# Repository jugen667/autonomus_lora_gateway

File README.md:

# autonomus_lora_gateway
Creation of an autonomous LoRa gateway

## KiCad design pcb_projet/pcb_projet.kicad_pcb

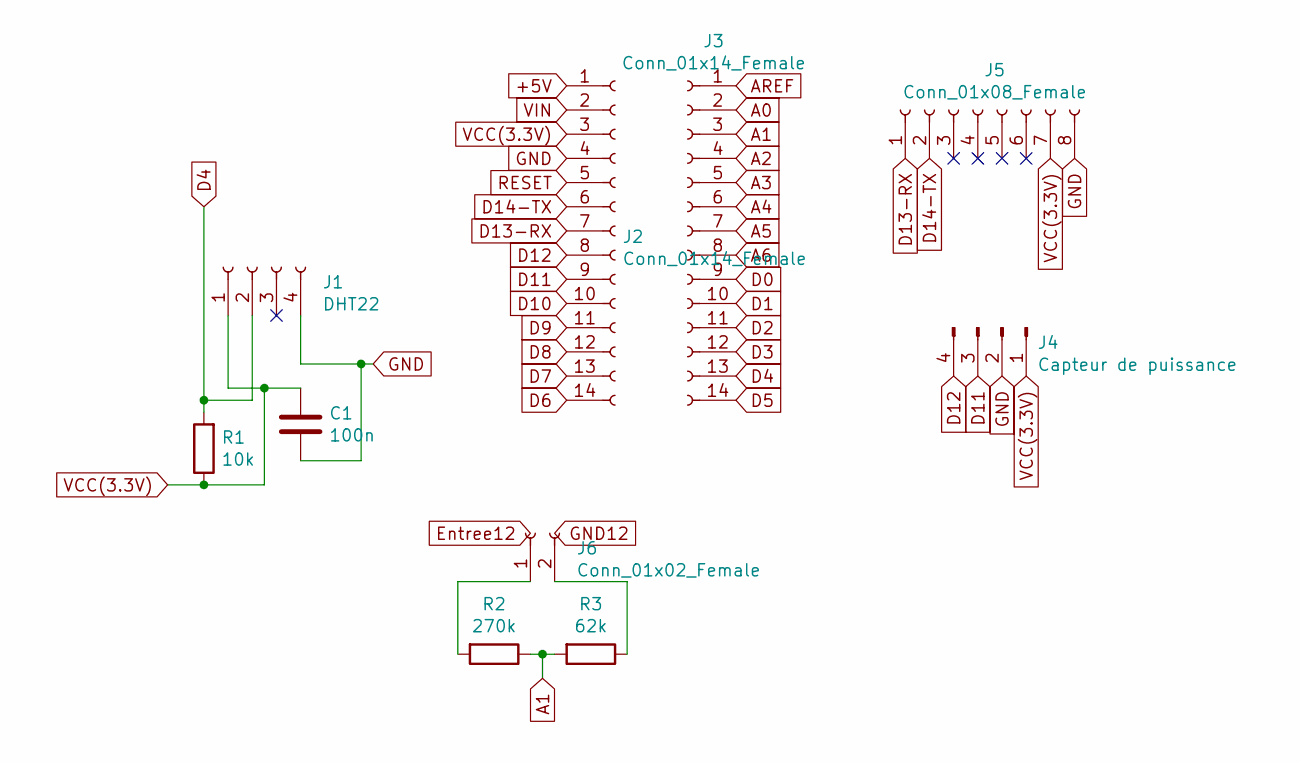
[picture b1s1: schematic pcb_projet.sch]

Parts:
C1: 100n; C_Disc_D7.5mm_W2.5mm_P5.00mm
J1: DHT22; PinHeader_1x04_P2.54mm_Vertical
J2, J3: Conn_01x14_Female; PinHeader_1x14_P2.54mm_Vertical
J4: Capteur de puissance; PinHeader_1x04_P2.54mm_Vertical
J5: Conn_01x08_Female; PinHeader_1x08_P2.54mm_Vertical
J6: Conn_01x02_Female; PinHeader_1x02_P2.54mm_Vertical
R1: 10k; R_Axial_DIN0204_L3.6mm_D1.6mm_P5.08mm_Horizontal
R2: 270k; R_Axial_DIN0204_L3.6mm_D1.6mm_P5.08mm_Horizontal
R3: 62k; R_Axial_DIN0204_L3.6mm_D1.6mm_P5.08mm_Horizontal

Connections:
+5V: J2.1
A0: J3.2
A1: J3.3, R2.1, R3.2
A2: J3.4
A3: J3.5
A4: J3.6
A5: J3.7
A6: J3.8
AREF: J3.1
D0: J3.9
D1: J3.10
D2: J3.11
D3: J3.12
D4: J1.2, J3.13, R1.2
D5: J3.14
D6: J2.14
D7: J2.13
D8: J2.12
D9: J2.11
D10: J2.10
D11: J2.9, J4.3
D12: J2.8, J4.4
D13-RX: J2.7, J5.1
D14-TX: J2.6, J5.2
GND: C1.2, J1.4, J2.4, J4.2, J5.8
unnamed: J6.1, R2.2
unnamed: J6.2, R3.1
RESET: J2.5
VCC(3.3V): C1.1, J1.1, J2.3, J4.1, J5.7, R1.1
VIN: J2.2

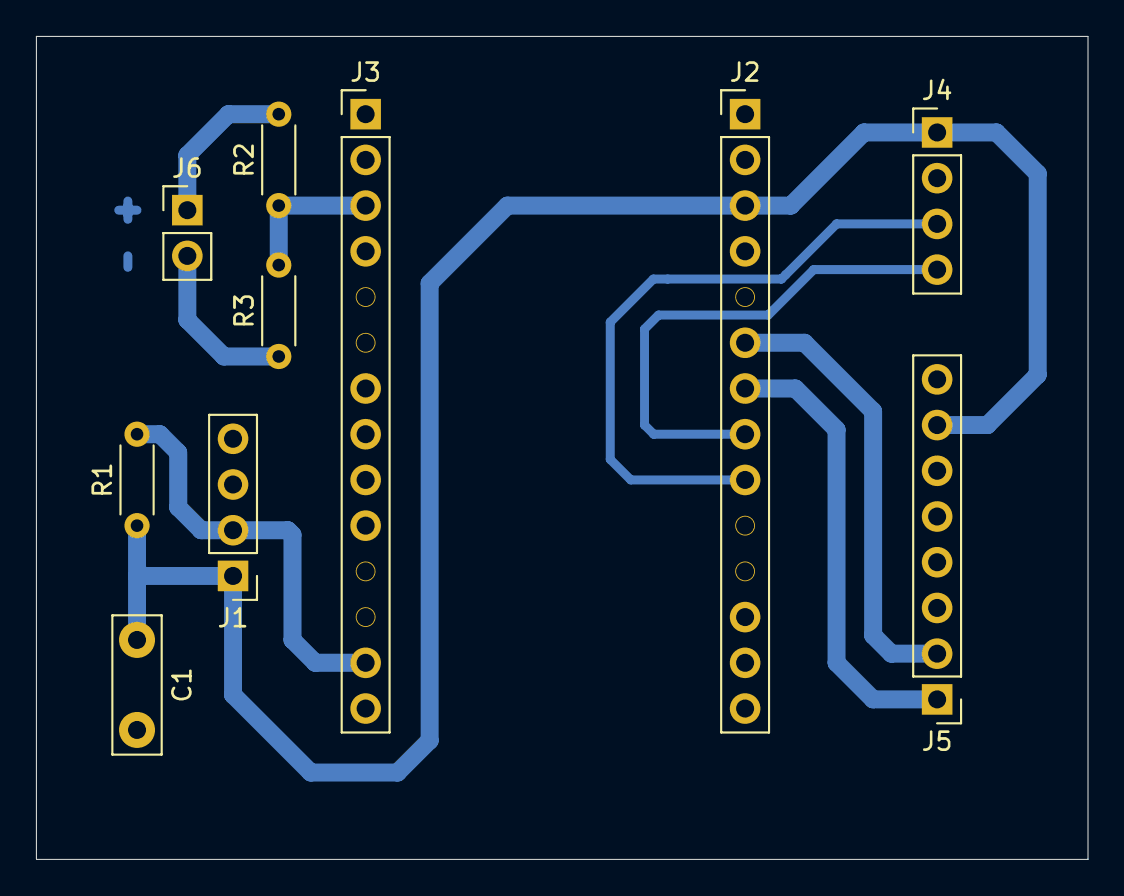
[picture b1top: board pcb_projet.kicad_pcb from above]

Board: 2 copper layers, 58.4 x 45.7 mm, 10 parts (0 on the bottom side), 10 nets.

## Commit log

2023-02-05 pcb creation files
2023-02-05 code lora
2023-02-06 update code
